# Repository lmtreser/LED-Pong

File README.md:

# Arduino LED Pong!

Simple juego al estilo *Pong!* con Arduino, LEDs y pulsadores. Se puede construir como un *shield* o con otro formato. Es un trabajo original de [@newsonator](https://www.instructables.com/Arduino-LED-Pong-Game-a-Fun-Electronics-Project/).

En [Tinkercad](https://www.tinkercad.com/things/hl14mxpcupM-arduino-led-pong) hay disponible un circuito de simulación publico.

## Licencia

Tanto la idea original como el firmware de **@newsonator** están protegidos por su respectiva licencia, por favor visitar los sitios web donde se encuentran alojados para mayor información. El resto del trabajo está protegido por la **Licencia MIT**. Puedes acceder a la versión original de la licencia (en inglés) a través del archivo [LICENSE](./LICENSE) o en línea en [The MIT License (MIT)](https://mit-license.org/). También proporcionamos una traducción no oficial desde [Wikipedia](https://es.m.wikipedia.org/wiki/Licencia_MIT#La_licencia):

Copyright (c) 2024 Lucas Martín Treser

Por la presente se concede permiso, libre de cargos, a cualquier persona que obtenga una copia de este software y de los archivos de documentación asociados (el "Software"), a utilizar el Software sin restricción, incluyendo sin limitación los derechos a usar, copiar, modificar, fusionar, publicar, distribuir, sublicenciar, y/o vender copias del Software, y a permitir a las personas a las que se les proporcione el Software a hacer lo mismo, sujeto a las siguientes condiciones:

El aviso de copyright anterior y este aviso de permiso se incluirán en todas las copias o partes sustanciales del Software.

EL SOFTWARE SE PROPORCIONA "COMO ESTÁ", SIN GARANTÍA DE NINGÚN TIPO, EXPRESA O IMPLÍCITA, INCLUYENDO PERO NO LIMITADO A GARANTÍAS DE COMERCIALIZACIÓN, IDONEIDAD PARA UN PROPÓSITO PARTICULAR E INCUMPLIMIENTO. EN NINGÚN CASO LOS AUTORES O PROPIETARIOS DE LOS DERECHOS DE AUTOR SERÁN RESPONSABLES DE NINGUNA RECLAMACIÓN, DAÑOS U OTRAS RESPONSABILIDADES, YA SEA EN UNA ACCIÓN DE CONTRATO, AGRAVIO O CUALQUIER OTRO MOTIVO, DERIVADAS DE, FUERA DE O EN CONEXIÓN CON EL SOFTWARE O SU USO U OTRO TIPO DE ACCIONES EN EL SOFTWARE.

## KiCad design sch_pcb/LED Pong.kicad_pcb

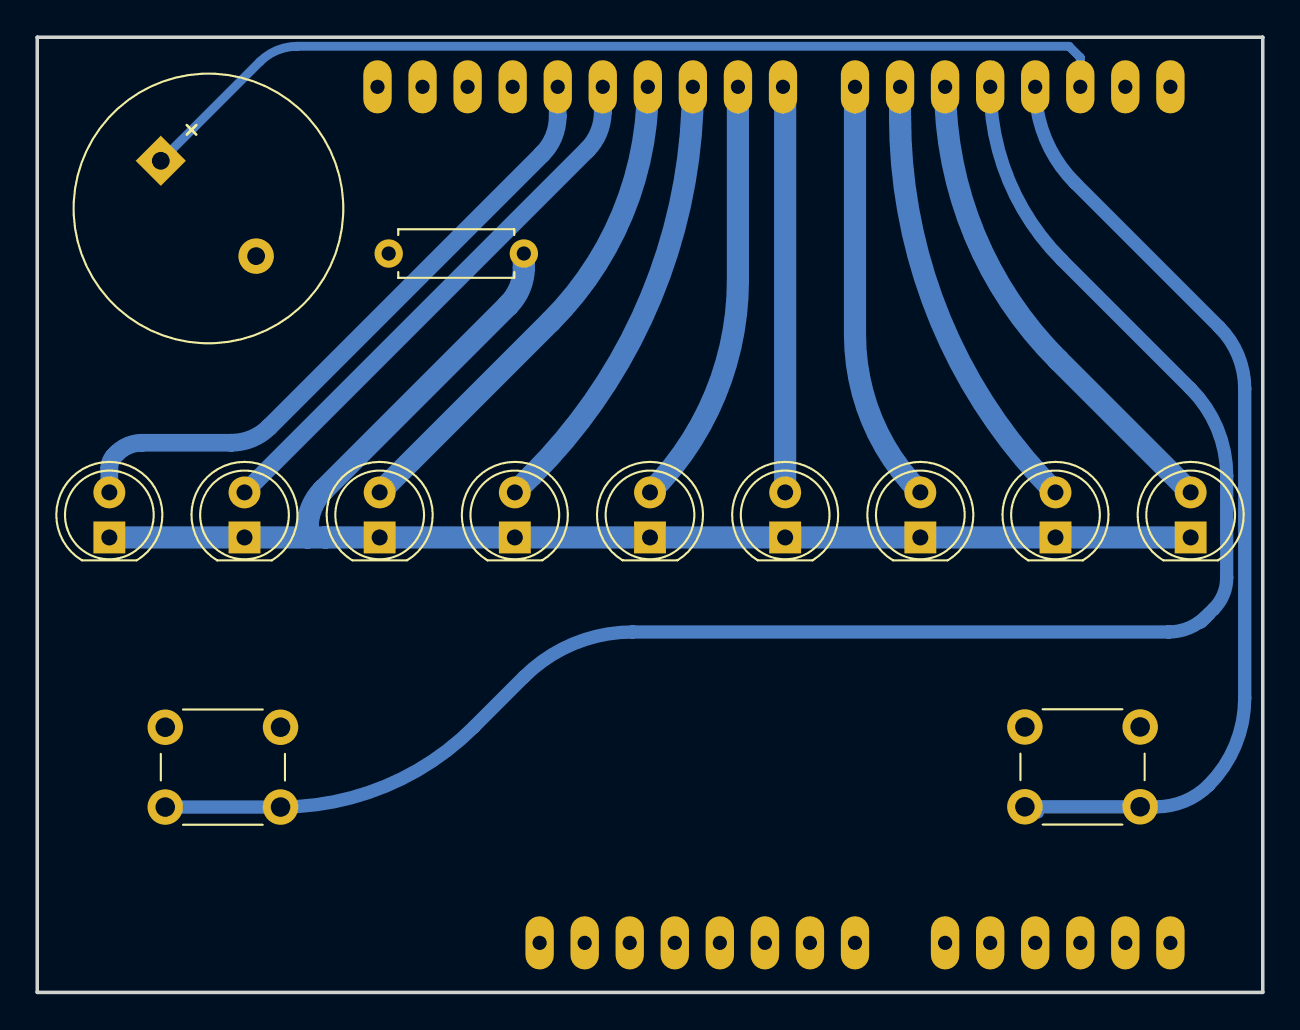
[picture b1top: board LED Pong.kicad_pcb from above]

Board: 2 copper layers, 69.1 x 53.8 mm, 14 parts (1 on the bottom side), 13 nets.

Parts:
A1: Arduino UNO; Arduino_UNO_R3_OVAL
BZ1: Buzzer; Buzzer_15x7.5RM7.6
D1, D2, D3, D4, D5, D6, D7, D8, D9: LED; LED_D5.0mm
R1: 100; R_Axial_DIN0207_L6.3mm_D2.5mm_P7.62mm_Horizontal
SW1, SW2: SW_Push; SW_PUSH_6mm

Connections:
/D5: A1.20 (D5), D1.2 (A)
/D6: A1.21 (D6), D2.2 (A)
/D7: A1.22 (D7), D3.2 (A)
/D8: A1.23 (D8), D4.2 (A)
/D9: A1.24 (D9), D5.2 (A)
/D10: A1.25 (D10), D6.2 (A)
/D11: A1.26 (D11), D7.2 (A)
/D12: A1.27 (D12), D8.2 (A)
/D13: A1.28 (D13), D9.2 (A)
GND: A1.6 (GND), A1.7 (GND), A1.29 (GND), BZ1.2 (+), R1.2, SW1.1, SW2.1
unnamed: A1.17 (D2), A1.18 (D3), BZ1.1 (-), SW1.2
unnamed: A1.19 (D4), SW2.2
unnamed: D1.1 (K), D2.1 (K), D3.1 (K), D4.1 (K), D5.1 (K), D6.1 (K), D7.1 (K), D8.1 (K), D9.1 (K), R1.1

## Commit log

2024-01-07 Documentación
2024-01-07 Arduino Firmware
2024-01-07 Kicad v7 esquemas y pcb
2024-01-10 update brd
2024-01-11 firmware clean
2024-01-11 Plantilla para fabricación
2024-01-11 update pcb
2024-01-15 update kicad libs
2024-01-29 update sch
2024-02-01 Create LICENSE
2024-02-25 update kicad v8
